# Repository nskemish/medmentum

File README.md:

<div align="center" id="toc">
  <ul style="list-style: none">
    <summary>
      <h1>MedMentum</h1><br>
      <h3 align="center">Automatski dozer za lekove</h3>
    </summary>
  </ul>
</div>

---

# Šta je to MedMentum?
**MedMentum** je revolucionarni sistem za automatsko doziranje lekova, osmišljen da transformiše način na koji pacijenti i zdravstveni radnici pristupaju terapijama. Ovaj inovativni uređaj kombiniuje najsavremeniju tehnologiju sa intuitivnim dizajnom kako bi omogućio precizno, sigurno i jednostavno doziranje lekova. MedMentum ne samo da olakšava svakodnevno uzimanje terapija, već i smanjuje rizik od ljudskih grešaka, čineći medicinsku negu pouzdanijom i efikasnijom. 💊✨

## Naša misija 

Naša misija je da revolucionišemo proces primene terapija kroz tehnološke inovacije. Želimo da smanjimo broj grešaka u doziranju lekova, povećamo svest o važnosti pravilnog uzimanja terapija i omogućimo pacijentima veću samostalnost u upravljanju svojim zdravljem. MedMentum je više od uređaja – to je alat koji podržava pacijente i zdravstvene radnike, čineći svakodnevne terapije jednostavnijim, sigurnijim i pristupačnijim. 

## Ciljevi 

1. **Preciznost**: MedMentum obezbeđuje tačno doziranje lekova u skladu sa propisanom terapijom, eliminišući mogućnost ljudske greške.   
2. **Sigurnost**: Pametni sigurnosni mehanizmi sprečavaju predoziranje ili propustanje doze, čime se povećava bezbednost pacijenata.   
3. **Pristupačnost**: Dizajniran je da bude jednostavan za korišćenje, kako bi odgovarao pacijentima svih uzrasta i zdravstvenih stanja.   
4. **Pouzdanost**: MedMentum pruža konzistentnu podršku, omogućavajući pacijentima da se oslanjaju na uređaj u svakodnevnom životu.   

## Ključne karakteristike 

- **Pametni uređaj za automatsko doziranje**: MedMentum automatski odmerava i dozira lekove prema unapred podešenom planu terapije. 
- **Integracija sa mobilnom aplikacijom**: Pacijenti i zdravstveni radnici mogu pratiti terapiju, primati podsetnici i prilagođavati doze putem jednostavne mobilne aplikacije.   
- **Notifikacije i podsetnici**: Sistem šalje obaveštenja za vreme uzimanja lekova, čime se smanjuje rizik od zaboravljanja. 
- **Sigurnosne funkcije**: Ugrađeni mehanizmi, poput zaključavanja i alarma, obezbeđuju da se lek uzima na pravi način i u pravo vreme.   
- **Moderan i ergonomski dizajn**: Uređaj je kompaktan, lak za nošenje i dizajniran da se uklopi u svakodnevni život korisnika. 

## Zašto je MedMentum neophodan? 

U današnjem svetu, gde su terapije sve složenije, a pacijenti često moraju da uzimaju više lekova dnevno, MedMentum predstavlja rešenje koje pojednostavljuje ovaj proces. Posebno je koristan za starije pacijente, one sa hroničnim bolestima ili pacijente koji imaju poteškoća u praćenju terapija. Zahvaljujući svojim pametnim funkcijama, MedMentum ne samo da poboljšava kvalitet života pacijenata, već i olakšava posao zdravstvenim radnicima, smanjujući opterećenje i rizik od grešaka. 🌍💪  

**MedMentum** je više od tehnologije – to je korak ka budućnosti u kojoj su terapije bezbednije, preciznije i pristupačnije za sve.

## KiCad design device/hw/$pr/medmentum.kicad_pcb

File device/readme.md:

# Projektna dokumentacija za uređaj

Ovaj folder sadrži sve fajlove i dokumentaciju vezanu za razvoj uređaja, uključujući hardverske komponente, mehanički dizajn i firmware.

## Struktura foldera

- **/hw**: Sadrži sve fajlove vezane za hardverski dizajn uređaja.
	- `$d/` - Folder sa simbolima, otiscima i 3D modelima.
	- `$bk/` - Folder sa rezervnim kopijama fajlova.
	- `$ds/` - Folder sa tehničkim dokumentacijama komponenti.
	- `$pr/` - Folder sa projektnim fajlovima.

- **/mh**: Sadrži fajlove vezane za mehanički dizajn uređaja.
  - `step/` - Modeli mehaničkih dijelova.
  - `elev/` - Kote dimenzija modela.
  - `stl/` - STL fajlovi za 3D štampu.

- **/fw**: Sadrži izvorni kod i dokumentaciju za firmware uređaja.
  - `src/` - Izvorni kod firmware-a.
    - `main.c` - Glavni programski kod.
    - `drivers/` - Drajveri za periferije.
  - `README.md` - Dokumentacija specifična za firmware.
  - `build/` - Kompajlirani fajlovi (opciono).

## Kako koristiti ovaj folder

### **Hardver**: 
Za pregled shematskih dijagrama i PCB dizajna, otvorite odgovarajuće fajlove u **`/hw`** folderu. 
Gerber fajlovi se mogu koristiti za naručivanje PCB-a.
> [!NOTE]
> Za otvaranje ovih fajlova potrebno je imati najnoviju verziju [KiCad-a](https://www.kicad.org/).

### **Mehanika**: 
3D modeli i 2D crteži se nalaze u **`/mh`** folderu. STL fajlovi su spremni za 3D štampu.

### **Firmware**: 
Izvorni kod firmware-a se nalazi u **`/fw/src`** folderu. Pratite uputstva u `readme.md` za kompilaciju i upload firmware-a na uređaj.

---

Za sva pitanja ili dodatne informacije, kontaktirajte:

- **Ognjen Guteša**  
  heyognjen@icloud.com  |  +381 63 532178

---
> [!WARNING]
> Ova dokumentacija je u razvoju i može biti ažurirana tokom projekta.

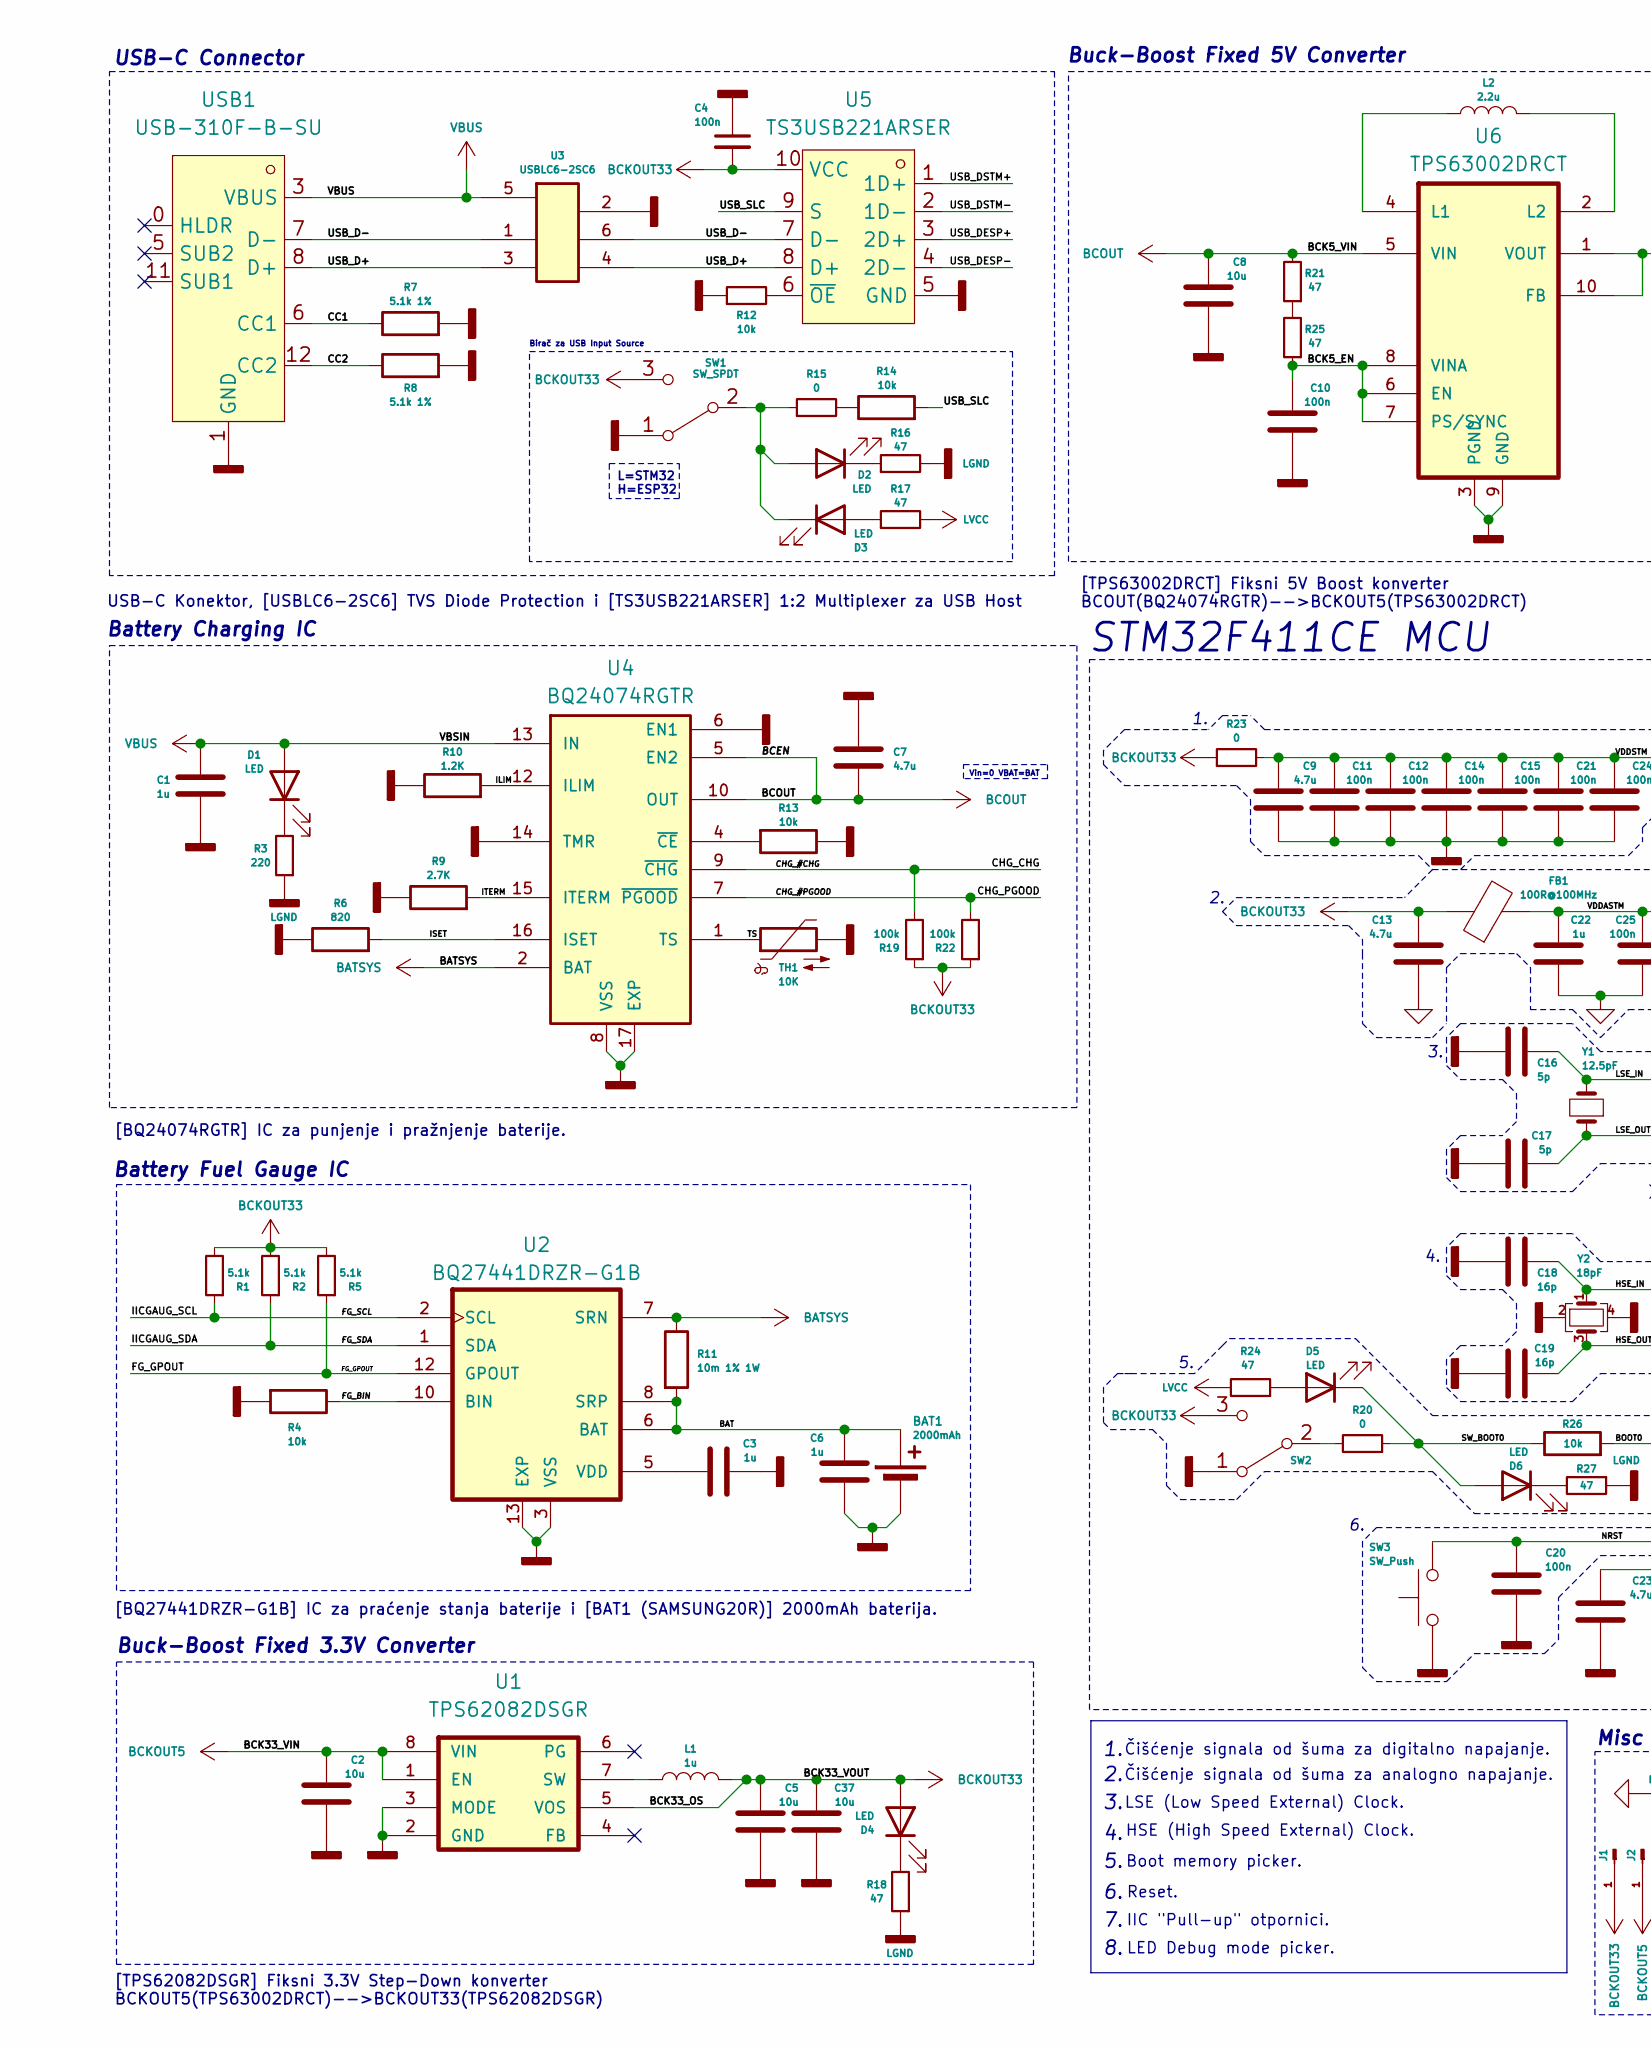
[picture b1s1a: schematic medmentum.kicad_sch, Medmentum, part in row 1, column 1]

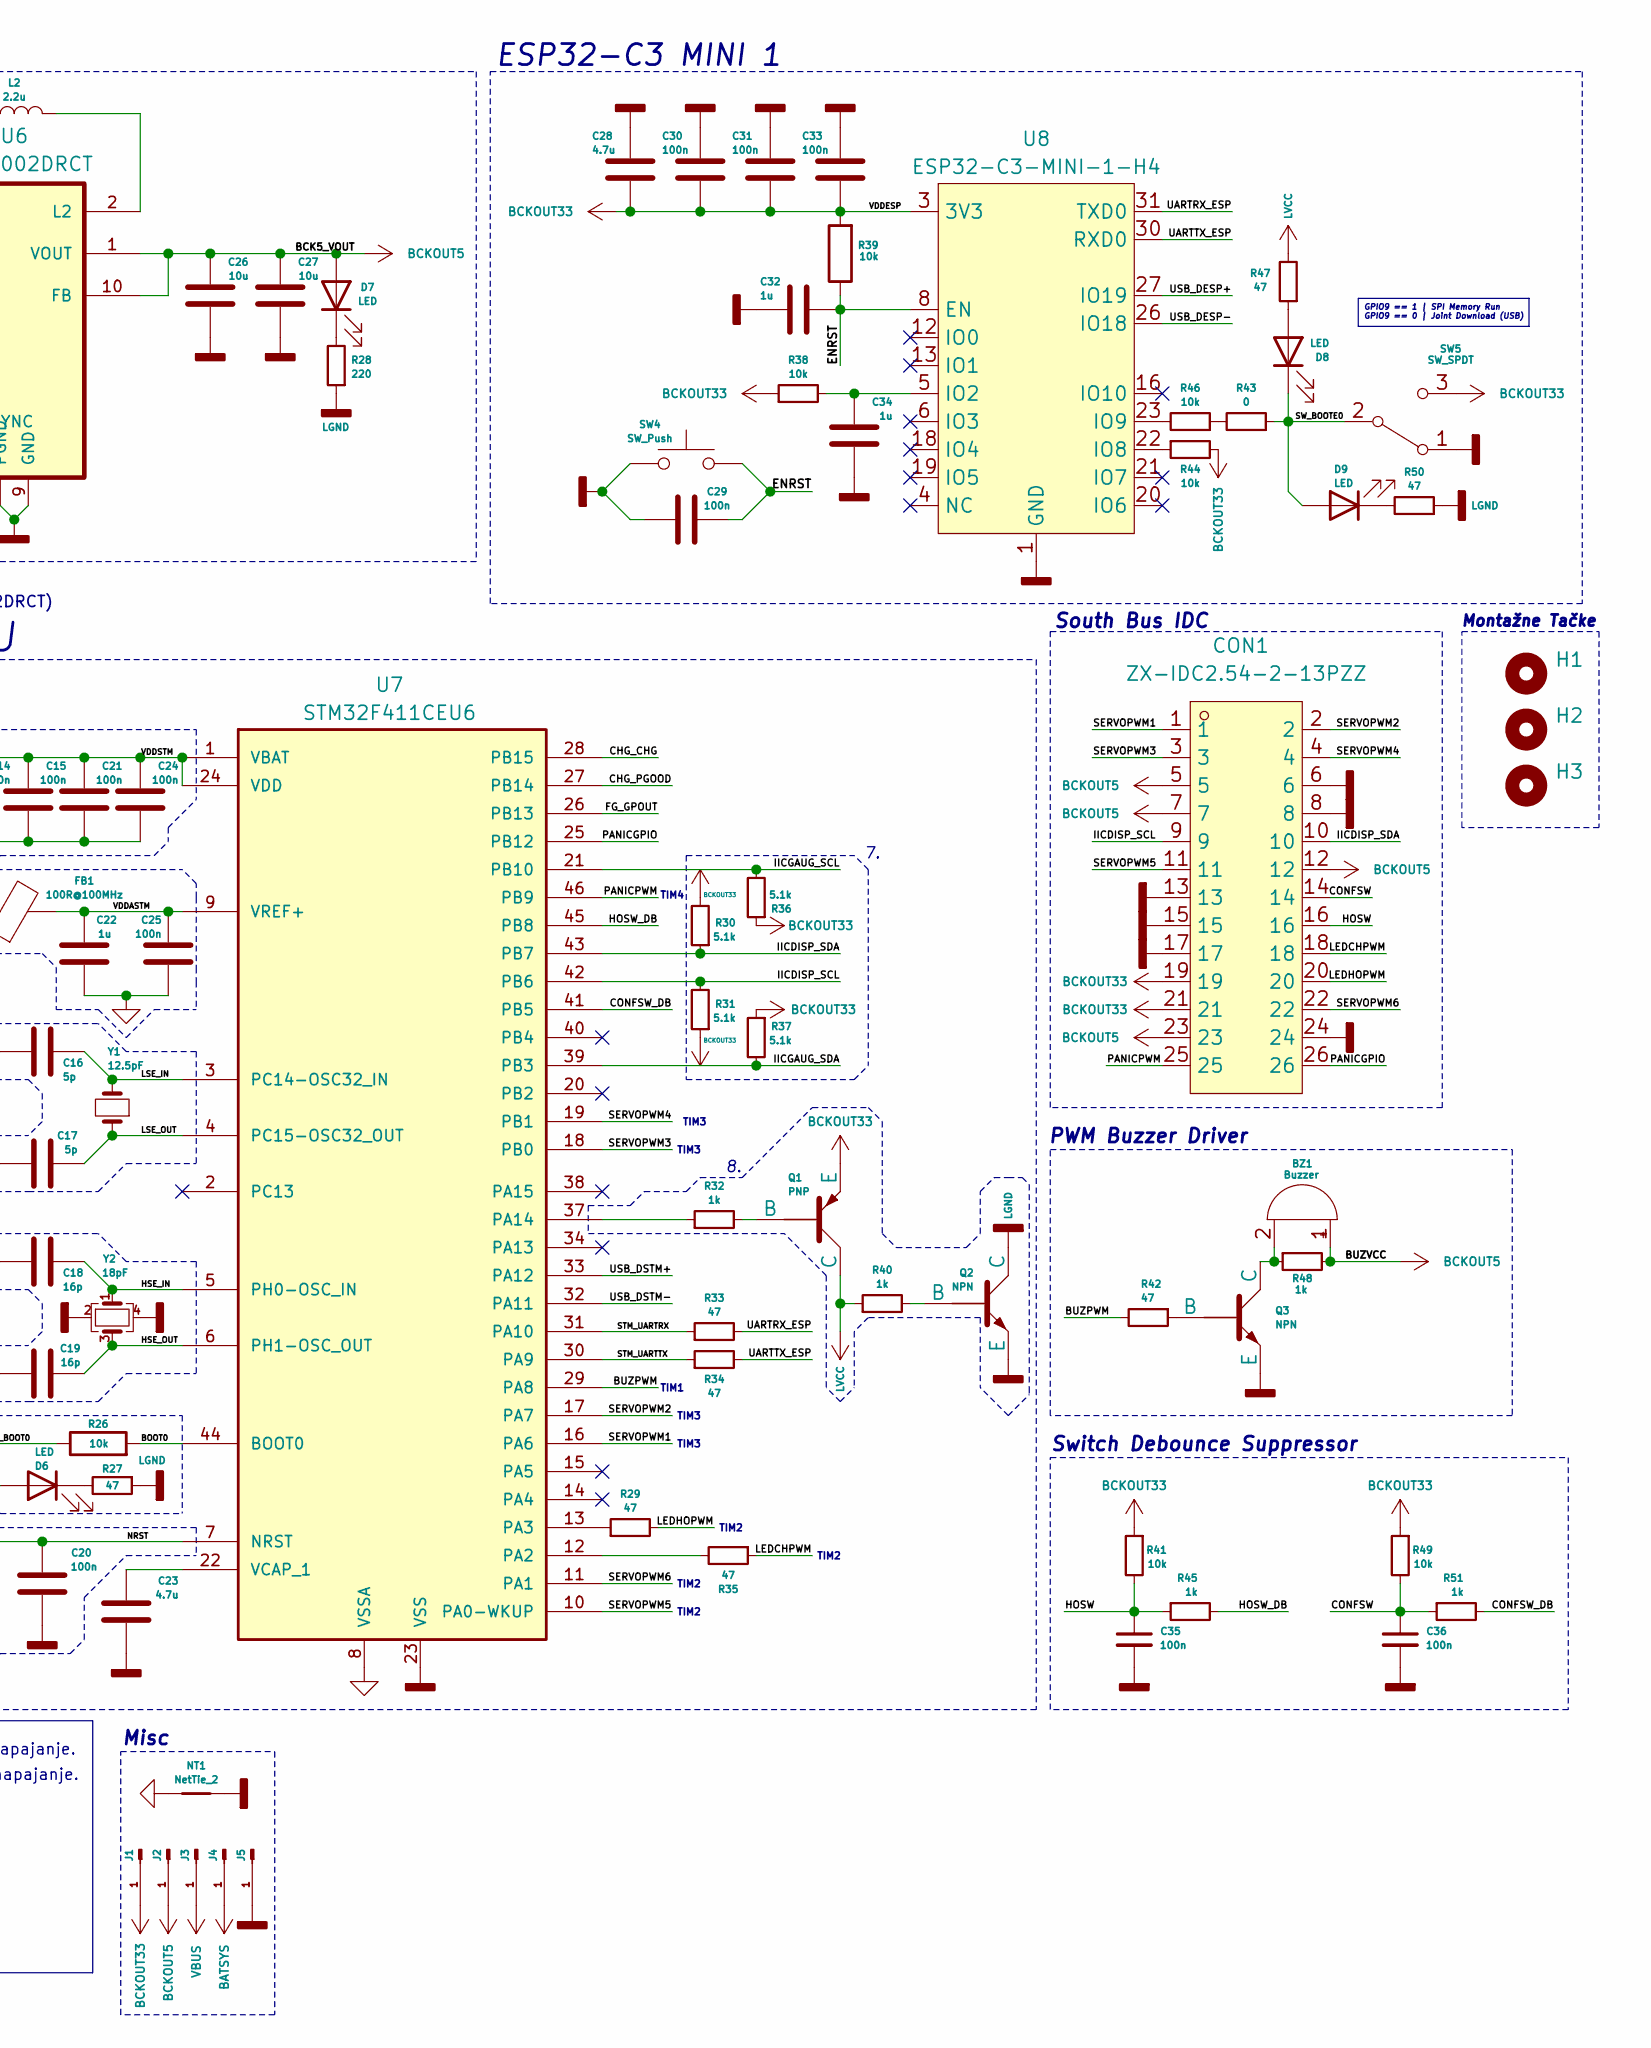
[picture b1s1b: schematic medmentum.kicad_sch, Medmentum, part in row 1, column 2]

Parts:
BAT1: 2000mAh; BATTERY-SMD_18650-1S-L77.1-W20.7-1; LCSCPart C5371778
BZ1: Buzzer; BUZ-TH_BD17.0-P10.00-D0.8; LCSCPart C76872
C1, C3, C6, C22, C32, C34: 1u; C_0603_1608Metric; LCSCPart C15849
C2, C5, C8, C26, C27, C37: 10u; C_0805_2012Metric; LCSCPart C15850
C4, C10, C11, C12, C14, C15, C20, C21, C24, C25, C29, C30, C31, C33, C35, C36: 100n; C_0603_1608Metric; LCSCPart C14663
C7, C9, C13, C23, C28: 4.7u; C_0805_2012Metric; LCSCPart C1779
C16, C17: 5p; C_0402_1005Metric; LCSCPart C880630
C18, C19: 16p; C_0402_1005Metric; LCSCPart C48836
CON1: ZX-IDC2.54-2-13PZZ; IDC-TH_26P-P2.54_ZX-IDC2.54-2-13PZZ; LCSCPart C7501247
D1, D4, D7: LED; LED_0805_2012Metric; LCSCPart C2297
D2, D3, D5, D6, D8, D9: LED; LED_0603_1608Metric; LCSCPart C2290
FB1: 100R@100MHz; L_0805_2012Metric; LCSCPart C1015
H1, H2, H3: MountingHole_2.5mm
J1, J2, J3, J4, J5: Conn_01x01_Pin; EPMM
L1: 1u; C_0603_1608Metric; LCSCPart C15849
L2: 2.2u; L_1008_2520Metric; LCSCPart C3002551
NT1: NetTie_2; NetTie-2_SMD_Pad0.5mm
Q1: PNP; SOT-23; LCSCPart C2143
Q2, Q3: NPN; SOT-23; LCSCPart C20526
R1, R2, R5, R30, R31, R36, R37: 5.1k; R_0402_1005Metric; LCSCPart C25905
R3, R28: 220; R_0603_1608Metric; LCSCPart C22962
R4, R12, R13, R14, R26, R38, R39, R41, R44, R46, R49: 10k; R_0402_1005Metric; LCSCPart C25744
R6: 820; R_0603_1608Metric; LCSCPart C23253
R7, R8: 5.1k 1%; R_0402_1005Metric; LCSCPart C25905
R9: 2.7K; R_0603_1608Metric; LCSCPart C13167
R10: 1.2K; R_0603_1608Metric; LCSCPart C22765
R11: 10m 1% 1W; R_1206_3216Metric; LCSCPart C601085
R15, R20, R23, R43: 0; R_0805_2012Metric; LCSCPart C17477
R16, R17, R18, R21, R24, R25, R27, R29, R33, R34, R35, R42, R47, R50: 47; R_0603_1608Metric; LCSCPart C23182
R19, R22: 100k; R_0603_1608Metric; LCSCPart C25803
R32, R40, R45, R48, R51: 1k; R_0603_1608Metric; LCSCPart C14676
SW1, SW2, SW5: SW_SPDT; SW-SMD_K3-1235S-K1; LCSCPart C92660
SW3, SW4: SW_Push; KEY-SMD_4P-L6.0-W6.0-P4.50-LS10.0; LCSCPart C83916
TH1: 10K; R_0603_1608Metric; LCSCPart C13564
U1: TPS62082DSGR; LCSCPart C485809
U2: BQ27441DRZR-G1B; LCSCPart C473374
U3: USBLC6-2SC6; LCSCPart C7519
U4: BQ24074RGTR; LCSCPart C54313
U5: TS3USB221ARSER; LCSC Part C128396
U6: TPS63002DRCT; TPS63002DRCR; LCSCPart C116655
U7: STM32F411CEU6; LCSCPart C60420
U8: ESP32-C3-MINI-1-H4; LCSCPart C2934569
USB1: USB-310F-B-SU; LCSCPart C309365
Y1: 12.5pF; Crystal_SMD_3215-2Pin_3.2x1.5mm; LCSCPart C130253
Y2: 18pF; Crystal_SMD_3225-4Pin_3.2x2.5mm; LCSCPart C179641

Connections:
/BAT: BAT1.1 (+), C6.2, R11.2, U2.6 (BAT), U2.8 (SRP)
/BCK5_EN: C10.2, R25.1, U6.6 (EN), U6.7 (PS/SYNC), U6.8 (VINA)
/BOOT0: R26.2, U7.44 (BOOT0)
/BUZPWM: R42.2, U7.29 (PA8)
/CC1: R7.1, USB1.6 (CC1)
/CC2: R8.1, USB1.12 (CC2)
/CHG_#CHG: R19.2, U4.9 (~CHG), U7.28 (PB15)
/CHG_#PGOOD: R22.2, U4.7 (~PGOOD), U7.27 (PB14)
/CONFSW: C36.1, CON1.14, R49.2, R51.1
/CONFSW_DB: R51.2, U7.41 (PB5)
/ENRST: C29.1, C32.1, R39.1, SW4.1, U8.8 (EN)
/FG_BIN: R4.1, U2.10 (BIN)
/FG_GPOUT: R5.1, U2.12 (GPOUT), U7.26 (PB13)
/FG_SCL: R1.1, R36.2, U2.2 (SCL), U7.21 (PB10)
/FG_SDA: R2.1, R37.2, U2.1 (SDA), U7.39 (PB3)
/HOSW: C35.1, CON1.16, R41.2, R45.1
/HOSW_DB: R45.2, U7.45 (PB8)
/HSE_IN: C18.1, U7.5 (PH0-OSC_IN), Y2.1
/HSE_OUT: C19.2, U7.6 (PH1-OSC_OUT), Y2.3
/IICDISP_SCL: CON1.9, R31.2, U7.42 (PB6)
/IICDISP_SDA: CON1.10, R30.1, U7.43 (PB7)
/ILIM: R10.2, U4.12 (ILIM)
/ISET: R6.2, U4.16 (ISET)
/ITERM: R9.2, U4.15 (ITERM)
/LEDCHPWM: CON1.18, R35.1
/LEDHOPWM: CON1.20, R29.2
/LSE_IN: C16.1, U7.3 (PC14-OSC32_IN), Y1.2
/LSE_OUT: C17.2, U7.4 (PC15-OSC32_OUT), Y1.1
/NRST: C20.2, SW3.2, U7.7 (NRST)
/PANICGPIO: CON1.26, U7.25 (PB12)
/PANICPWM: CON1.25, U7.46 (PB9)
/SERVOPWM1: CON1.1, U7.16 (PA6)
/SERVOPWM2: CON1.2, U7.17 (PA7)
/SERVOPWM3: CON1.3, U7.18 (PB0)
/SERVOPWM4: CON1.4, U7.19 (PB1)
/SERVOPWM5: CON1.11, U7.10 (PA0-WKUP)
/SERVOPWM6: CON1.22, U7.11 (PA1)
/STM_UARTRX: R33.1, U7.31 (PA10)
/STM_UARTTX: R34.1, U7.30 (PA9)
/SW_BOOT0: D5.1 (K), D6.2 (A), R20.1, R26.1
/SW_BOOTE0: D8.1 (K), D9.2 (A), R43.1, SW5.2 (B)
/TS: TH1.1, U4.1 (TS)
/UARTRX_ESP: R33.2, U8.31 (TXD0)
/UARTTX_ESP: R34.2, U8.30 (RXD0)
/USB_D+: U3.3, U3.4, U5.8 (D+), USB1.8 (D+), USB1.10 (D+)
/USB_D-: U3.1, U3.6, U5.7 (D-), USB1.7 (D-), USB1.9 (D-)
/USB_DESP+: U5.3 (2D+), U8.27 (IO19)
/USB_DESP-: U5.4 (2D-), U8.26 (IO18)
/USB_DSTM+: U5.1 (1D+), U7.33 (PA12)
/USB_DSTM-: U5.2 (1D-), U7.32 (PA11)
/USB_SLC: R14.2, U5.9 (S)
/VDDASTM: C22.2, C25.2, FB1.2, U7.9 (VREF+)
BATSYS: J4.1, R11.1, U2.7 (SRN), U4.2 (BAT), U4.3 (BAT)
BCKOUT5: BZ1.1 (+), C2.2, C26.2, C27.2, CON1.5, CON1.7, CON1.12, CON1.23, D7.2 (A), J2.1, R48.2, U1.1 (EN), U1.8 (VIN), U6.1 (VOUT), U6.10 (FB)
BCKOUT33: C4.2, C5.2, C13.2, C28.1, C30.1, C31.1, C33.1, C37.2, CON1.19, CON1.21, D4.2 (A), FB1.1, J1.1, L1.2, Q1.3 (E), R1.2, R2.2, R5.2, R19.1, R22.1, R23.1, R30.2, R31.1, R36.1, R37.1, R38.1, R39.2, R41.1, R44.2, R49.1, SW1.3 (C), SW2.3 (C), SW5.3 (C), U1.5 (VOS), U5.10 (VCC), U8.3 (3V3)
BCOUT: C7.2, C8.2, R21.2, U4.5 (EN2), U4.10 (OUT), U4.11 (OUT), U6.5 (VIN)
GNDA: C13.1, C22.1, C25.1, NT1.1, U7.8 (VSSA)
GNDD: BAT1.2 (-), C1.2, C2.1, C3.2, C4.1, C5.1, C6.1, C7.1, C8.1, C9.1, C10.1, C11.1, C12.1, C14.1, C15.1, C16.2, C17.1, C18.2, C19.1, C20.1, C21.1, C23.1, C24.1, C26.1, C27.1, C28.2, C29.2, C30.2, C31.2, C32.2, C33.2, C34.1, C35.2, C36.2, C37.1, CON1.6, CON1.8, CON1.13, CON1.15, CON1.17, CON1.24, J5.1, NT1.2, Q2.3 (E), Q3.3 (E), R4.2, R6.1, R7.2, R8.2, R9.1, R10.1, R12.1, R13.1, SW1.1 (A), SW2.1 (A), SW3.1, SW4.2, SW5.1 (A), TH1.2, U1.2 (GND), U1.3 (MODE), U1.9 (GND), U1.9_1 (GND), U1.9_2 (GND), U2.3 (VSS), U2.13 (EXP), U3.2, U4.6 (EN1), U4.8 (VSS), U4.14 (TMR), U4.17 (EXP), U4.18, U5.5 (GND), U6.3 (PGND), U6.9 (GND), U6.11 (PP), U6.12, U6.13, U6.14, U6.15, U7.23 (VSS), U7.35 (VSS), U7.47 (VSS), U7.49 (VSS), U7.50, U8.1 (GND), U8.2 (GND), U8.11 (GND), U8.14 (GND), U8.36 (GND), U8.37 (GND), U8.38 (GND), U8.39 (GND), U8.40 (GND), U8.41 (GND), U8.42 (GND), U8.43 (GND), U8.44 (GND), U8.45 (GND), U8.46 (GND), U8.47 (GND), U8.48 (GND), U8.49 (GND), U8.50 (GND), U8.51 (GND), U8.52 (GND), U8.53 (GND), USB1.1 (GND), USB1.2 (GND), USB1.15 (GND), USB1.16 (GND), Y2.2, Y2.4
LGND: Q2.1 (C), R3.1, R16.2, R18.1, R27.1, R28.1, R50.1
LVCC: Q1.1 (C), R17.2, R24.2, R40.1, R47.2
unnamed: BZ1.2 (-), Q3.1 (C), R48.1
unnamed: D1.1 (K), R3.2
unnamed: D2.2 (A), D3.1 (K), R15.1, SW1.2 (B)
unnamed: D2.1 (K), R16.1
unnamed: D3.2 (A), R17.1
unnamed: D4.1 (K), R18.2
unnamed: D5.2 (A), R24.1
unnamed: D6.1 (K), R27.2
unnamed: D7.1 (K), R28.2
unnamed: D8.2 (A), R47.1
unnamed: D9.1 (K), R50.2
unnamed: Q1.2 (B), R32.2
unnamed: Q2.2 (B), R40.2
unnamed: Q3.2 (B), R42.1
unnamed: R14.1, R15.2
unnamed: R21.1, R25.2
unnamed: R43.2, R46.1
unnamed: R20.2, SW2.2 (B)
unnamed: L1.1, U1.7 (SW)
unnamed: C3.1, U2.5 (VDD)
unnamed: R13.2, U4.4 (~CE)
unnamed: R12.2, U5.6 (~OE)
unnamed: L2.1, U6.4 (L1)
unnamed: L2.2, U6.2 (L2)
unnamed: R35.2, U7.12 (PA2)
unnamed: R29.1, U7.13 (PA3)
unnamed: R32.1, U7.37 (PA14)
unnamed: C23.2, U7.22 (VCAP_1)
unnamed: C34.2, R38.2, U8.5 (IO2)
unnamed: R44.1, U8.22 (IO8)
unnamed: R46.2, U8.23 (IO9)
VBUS: C1.1, D1.2 (A), J3.1, U3.5, U4.13 (IN), USB1.3 (VBUS), USB1.4 (VBUS), USB1.13 (VBUS), USB1.14 (VBUS)
VDD: C9.2, C11.2, C12.2, C14.2, C15.2, C21.2, C24.2, R23.2, U7.1 (VBAT), U7.24 (VDD), U7.36 (VDD), U7.48 (VDD)

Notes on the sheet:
Vin=0 VBAT=BAT
GPIO9 == 1 | SPI Memory Run GPIO9 == 0 | Joint Download (USB)
L=STM32 H=ESP32
TIM1
PWM Buzzer Driver
STM32F411CE MCU
Birač za USB Input Source
TIM4
IIC "Pull-up" otpornici.
TIM2
TIM3
Čišćenje signala od šuma za analogno napajanje.
LSE (Low Speed External) Clock.
Buck-Boost Fixed 5V Converter
Switch Debounce Suppressor
USB-C Konektor, [USBLC6-2SC6] TVS Diode Protection i [TS3USB221ARSER] 1:2 Multiplexer za USB Host
ESP32-C3 MINI 1
Battery Fuel Gauge IC
[BQ24074RGTR] IC za punjenje i pražnjenje baterije.
HSE (High Speed External) Clock.
Čišćenje signala od šuma za digitalno napajanje.
[TPS63002DRCT] Fiksni 5V Boost konverter BCOUT(BQ24074RGTR)-->BCKOUT5(TPS63002DRCT)
LED Debug mode picker.
Buck-Boost Fixed 3.3V Converter
Boot memory picker.
South Bus IDC
USB-C Connector
Misc
Battery Charging IC
[BQ27441DRZR-G1B] IC za praćenje stanja baterije i [BAT1 (SAMSUNG20R)] 2000mAh baterija.
[TPS62082DSGR] Fiksni 3.3V Step-Down konverter BCKOUT5(TPS63002DRCT)-->BCKOUT33(TPS62082DSGR)
Montažne Tačke
Reset.

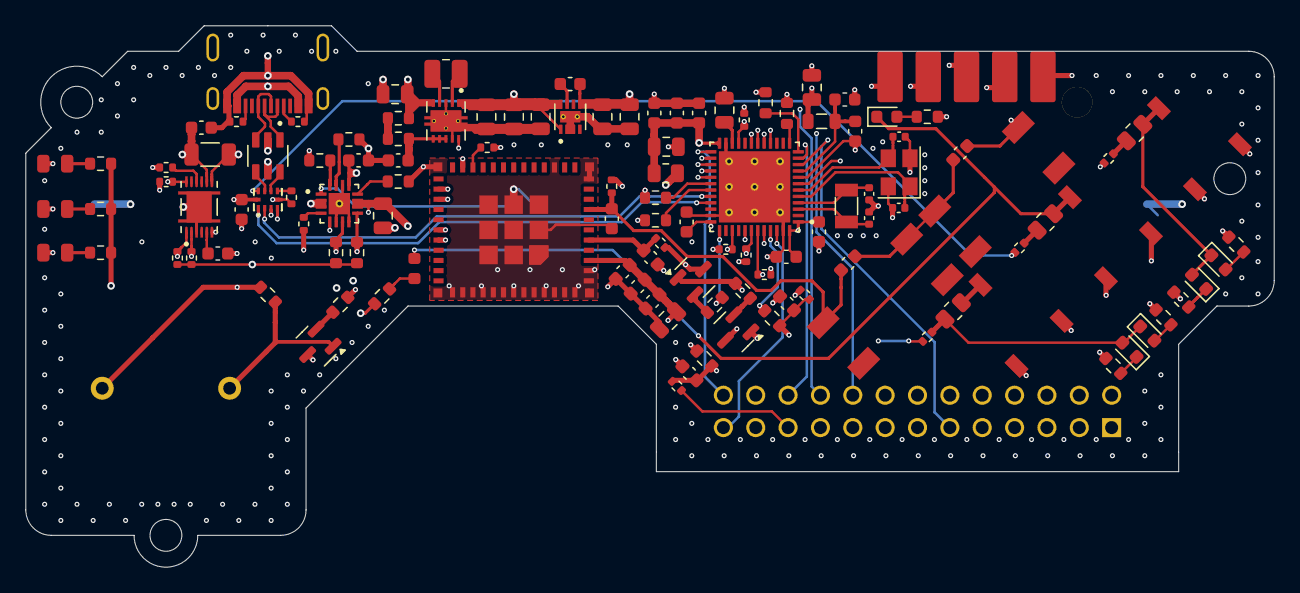
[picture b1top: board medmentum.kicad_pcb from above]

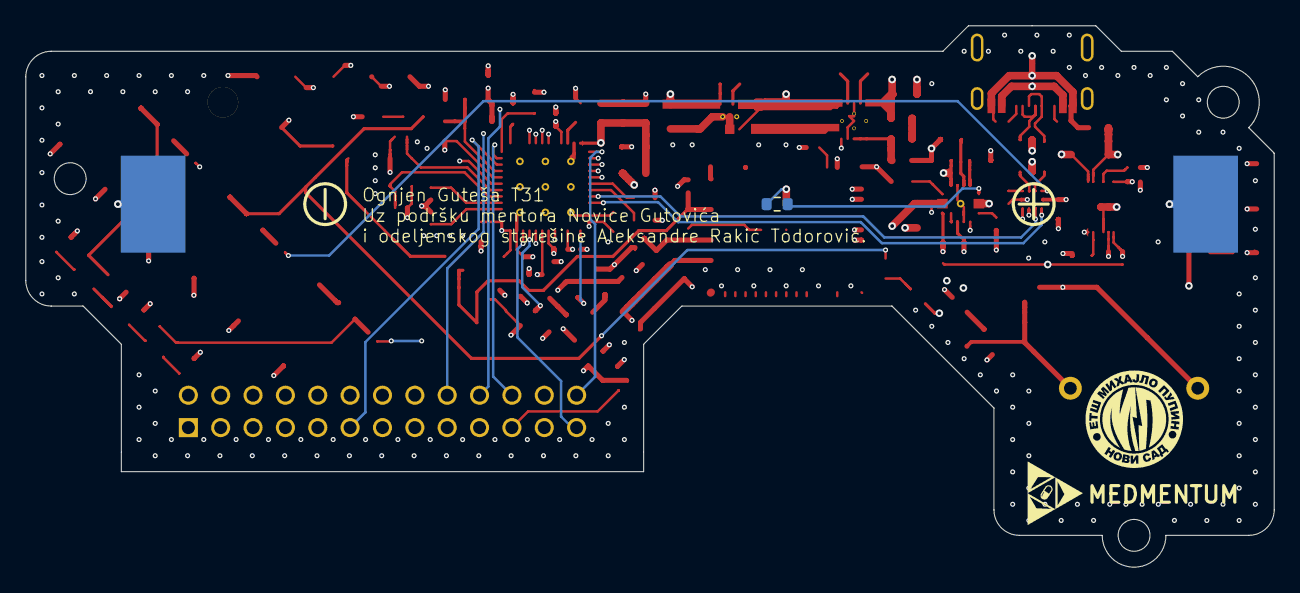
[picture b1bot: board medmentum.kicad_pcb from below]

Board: 6 copper layers, 98.0 x 42.5 mm, 132 parts (3 on the bottom side), 93 nets.

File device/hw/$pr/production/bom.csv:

Reference,Value,Footprint,Qty,DNP,LCSC Part
CON1,ZX-IDC2.54-2-13PZZ,fpl:IDC-TH_26P-P2.54_ZX-IDC2.54-2-13PZZ,1,,C7501247
BAT1,2000mAh,fpl:BATTERY-SMD_18650-1S-L77.1-W20.7-1,1,,C5371778
L2,2.2u,Inductor_SMD:L_1008_2520Metric,1,,C3002551
U8,ESP32-C3-MINI-1-H4,fpl:ESP32-C3-MINI-1-H4,1,,C2934569
"C16,C17",5p,Capacitor_SMD:C_0402_1005Metric,2,,C880630
R11,10m 1% 1W,Resistor_SMD:R_1206_3216Metric,1,,C601085
U1,TPS62082DSGR,fpl:TPS62082DSGR,1,,C485809
U2,BQ27441DRZR-G1B,fpl:BQ27441DRZR-G1B,1,,C473374
USB1,USB-310F-B-SU,fpl:USB-310F-B-SU,1,,C309365
Y2,18pF,Crystal:Crystal_SMD_3225-4Pin_3.2x2.5mm,1,,C179641
Y1,12.5pF,Crystal:Crystal_SMD_3215-2Pin_3.2x1.5mm,1,,C130253
U5,TS3USB221ARSER,fpl:TS3USB221ARSER,1,,C128396
U6,TPS63002DRCT,fpl:TPS63002DRCR,1,,C116655
"SW1,SW2,SW5",SW_SPDT,fpl:SW-SMD_K3-1235S-K1,3,,C92660
"SW3,SW4",SW_Push,fpl:KEY-SMD_4P-L6.0-W6.0-P4.50-LS10.0,2,,C83916
BZ1,Buzzer,fpl:BUZ-TH_BD17.0-P10.00-D0.8,1,,C76872
U7,STM32F411CEU6,fpl:STM32F411CEU6,1,,C60420
U4,BQ24074RGTR,fpl:BQ24074RGTR,1,,C54313
"C18,C19",16p,Capacitor_SMD:C_0402_1005Metric,2,,C48836
"R7,R8",5.1k 1%,Resistor_SMD:R_0402_1005Metric,2,,C25905
"R1,R2,R5,R30,R31,R36,R37",5.1k,Resistor_SMD:R_0402_1005Metric,7,,C25905
"R19,R22",100k,Resistor_SMD:R_0603_1608Metric,2,,C25803
"R4,R12,R13,R14,R26,R38,R39,R41,R44,R46,R49",10k,Resistor_SMD:R_0402_1005Metric,11,,C25744
R6,820,Resistor_SMD:R_0603_1608Metric,1,,C23253
"R16,R17,R18,R21,R24,R25,R27,R29,R33,R34,R35,R42,R47,R50",47,Resistor_SMD:R_0603_1608Metric,14,,C23182
"R3,R28",220,Resistor_SMD:R_0603_1608Metric,2,,C22962
R10,1.2K,Resistor_SMD:R_0603_1608Metric,1,,C22765
"Q2,Q3",NPN,Package_TO_SOT_SMD:SOT-23,2,,C20526
"R15,R20,R23,R43",0,Resistor_SMD:R_0805_2012Metric,4,,C17477
"C2,C5,C8,C26,C27,C37",10u,Capacitor_SMD:C_0805_2012Metric,6,,C15850
"C1,C3,C6,C22,C32,C34,L1",1u,Capacitor_SMD:C_0603_1608Metric,7,,C15849
"R32,R40,R45,R48,R51",1k,Resistor_SMD:R_0603_1608Metric,5,,C14676
"C4,C10,C11,C12,C14,C15,C20,C21,C24,C25,C29,C30,C31,C33,C35,C36",100n,Capacitor_SMD:C_0603_1608Metric,16,,C14663
TH1,10K,Resistor_SMD:R_0603_1608Metric,1,,C13564
R9,2.7K,Resistor_SMD:R_0603_1608Metric,1,,C13167
U3,USBLC6-2SC6,fpl:USBLC6-2SC6,1,,C7519
"D1,D4,D7",LED,LED_SMD:LED_0805_2012Metric,3,,C2297
"D2,D3,D5,D6,D8,D9",LED,LED_SMD:LED_0603_1608Metric,6,,C2290
Q1,PNP,Package_TO_SOT_SMD:SOT-23,1,,C2143
"C7,C9,C13,C23,C28",4.7u,Capacitor_SMD:C_0805_2012Metric,5,,C1779
FB1,100R@100MHz,Inductor_SMD:L_0805_2012Metric,1,,C1015
"J1,J2,J3,J4,J5",Conn_01x01_Pin,fpl:EPMM,5,,

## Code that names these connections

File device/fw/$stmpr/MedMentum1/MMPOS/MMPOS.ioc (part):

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Mcu.Name=STM32F411C(C-E)Ux
Mcu.Package=UFQFPN48
Mcu.UserName=STM32F411CEUx
PA0-WKUP.Signal=S_TIM2_CH1_ETR
PA1.Signal=S_TIM2_CH2
PA10.Mode=Asynchronous
PA10.Signal=USART1_RX
PA11.Mode=Host_Only
PA11.Signal=USB_OTG_FS_DM
PA12.Mode=Host_Only
PA12.Signal=USB_OTG_FS_DP
PA13.Signal=GPIO_Output
PA14.Signal=GPIO_Output
PA2.Signal=S_TIM2_CH3
PA3.Signal=S_TIM2_CH4
PA6.Signal=S_TIM3_CH1
PA7.Signal=S_TIM3_CH2
PA8.Signal=S_TIM1_CH1
PA9.Mode=Asynchronous
PA9.Signal=USART1_TX
PB0.Signal=S_TIM3_CH3
PB1.Signal=S_TIM3_CH4
PB10.Mode=I2C
PB10.Signal=I2C2_SCL
PB12.Signal=GPIO_Input
PB13.Signal=GPIO_Input
PB14.Signal=GPIO_Input
PB15.Signal=GPIO_Input
PB3.Mode=I2C
PB3.Signal=I2C2_SDA
PB5.Signal=GPIO_Input
PB6.Mode=I2C
PB6.Signal=I2C1_SCL
PB7.Mode=I2C
PB7.Signal=I2C1_SDA
PB8.Signal=GPIO_Input
PB9.Signal=S_TIM4_CH4
PC14-OSC32_IN.Mode=LSE-External-Oscillator
PC14-OSC32_IN.Signal=RCC_OSC32_IN
PC15-OSC32_OUT.Mode=LSE-External-Oscillator
PC15-OSC32_OUT.Signal=RCC_OSC32_OUT
PH0\ -\ OSC_IN.Mode=HSE-External-Oscillator
PH0\ -\ OSC_IN.Signal=RCC_OSC_IN
PH1\ -\ OSC_OUT.Mode=HSE-External-Oscillator
PH1\ -\ OSC_OUT.Signal=RCC_OSC_OUT
RCC.HSE_VALUE=25000000
RCC.SYSCLKFreq_VALUE=16000000
board=custom

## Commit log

2025-01-13 Add File Structure
2025-01-13 .gitkeep
2025-01-14 Update Repository
2025-01-14 Banana.png
2025-01-14 Dokumentacija
2025-01-15 Tekst
2025-01-15 Add sheets
2025-01-16 Dokumentacija 1
2025-01-19 Raspored
2025-01-21 Sheets
2025-01-21 .gitignore
2025-01-21 application
2025-01-21 backup
2025-01-21 remove
2025-01-21 pages
2025-01-27 New-Sheet
2025-02-26 Aplikacija
2025-03-05 Evo dizajna
2025-03-05 Finalni kod za dizajn Medmentum app
    Probaj pa javi
2025-03-05 Malo sam ti sortirao sve lepi moj
2025-03-08 Update README.md
    eo reseno
2025-03-09 Update issue templates
2025-03-09 Popravljen logo
2025-03-09 Popravljeni logo-i u SVG formatu.
2025-03-11 readme
2025-03-11 Zavrsena aplikacija
2025-03-11 app1
    brišem jer je pogrešan i bespotreban
2025-03-11 Pozadine u svim formatima
